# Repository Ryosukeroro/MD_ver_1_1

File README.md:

# MD_ver_1_1
## 偉大なるMD_ver_1_1とは...
モータードライバーを製作して、初めて成功したときのデータです。

# ダウンロード
ダウンロードされる際は、以下のコマンドを実行してください。
```
git clone https://github.com/Ryosukeroro/MD_ver_1_1.git
```

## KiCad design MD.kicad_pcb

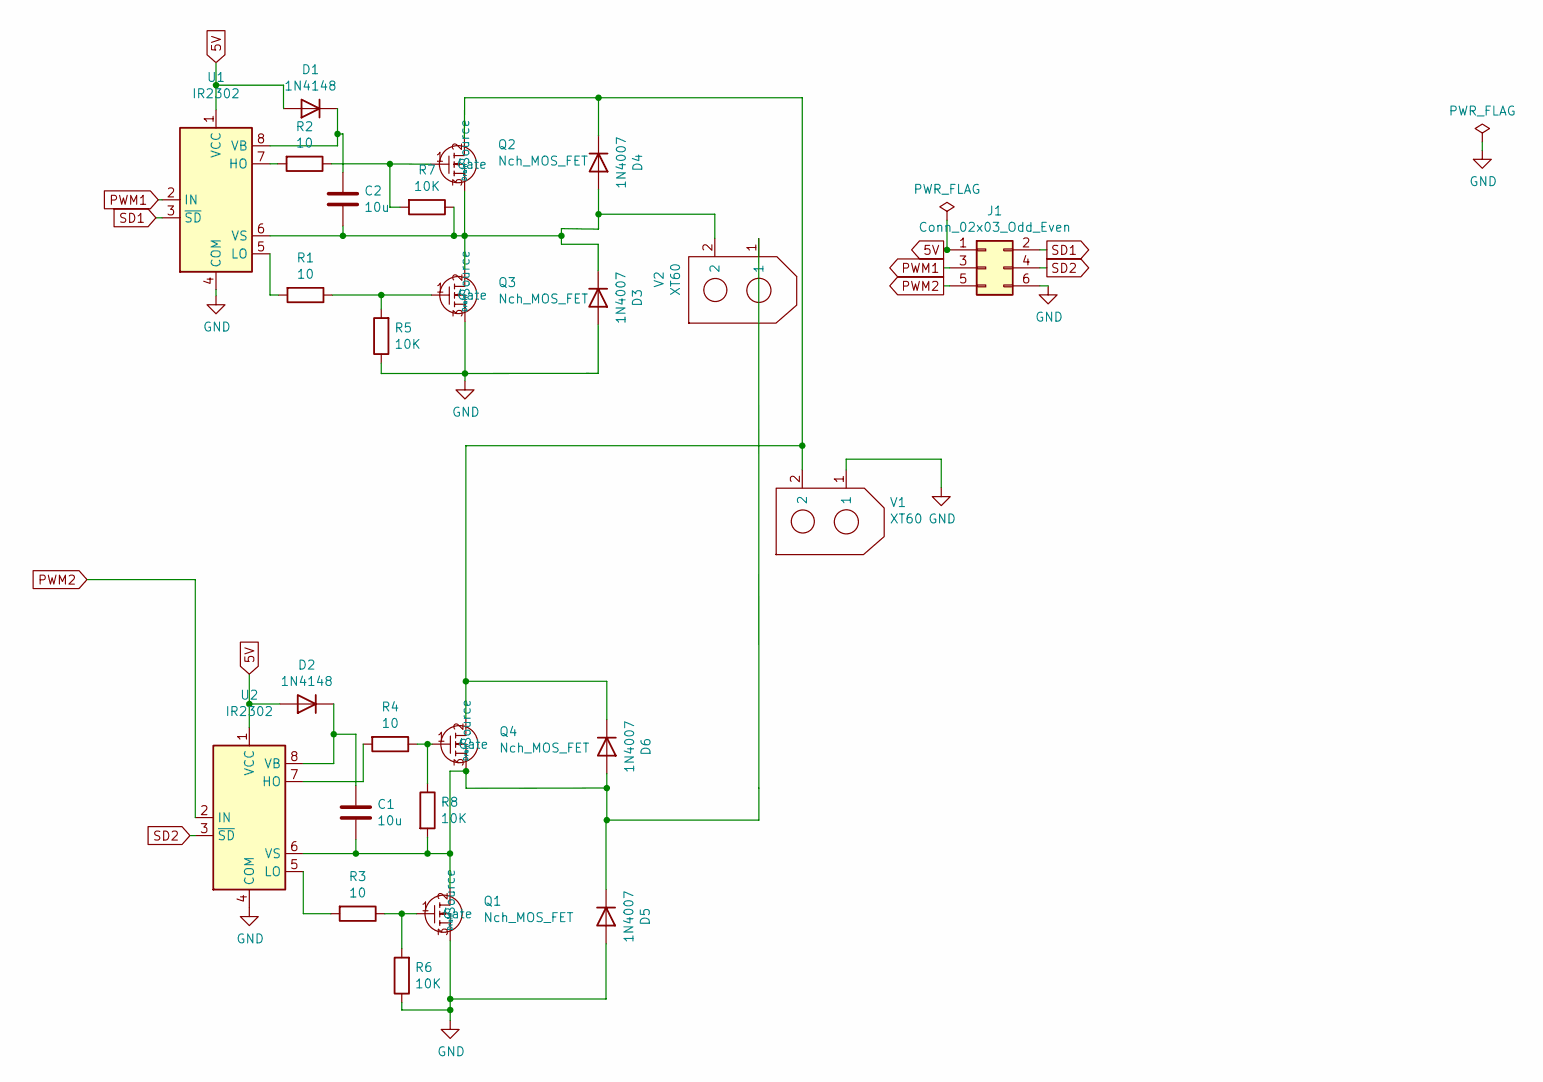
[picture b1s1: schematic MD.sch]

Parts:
C1, C2: 10u; C_Axial_L3.8mm_D2.6mm_P7.50mm_Horizontal
D1, D2: 1N4148; D_DO-35_SOD27_P7.62mm_Horizontal
D3, D4, D5, D6: 1N4007; D_DO-41_SOD81_P10.16mm_Horizontal
J1: Conn_02x03_Odd_Even; PinSocket_2x03_P2.54mm_Vertical
Q1, Q2, Q3, Q4: Nch_MOS_FET; TO-126-3_Vertical
R1, R2, R3, R4: 10; R_2512_6332Metric
R5, R6, R7: 10K; R_0805_2012Metric
R8: 10K; R_Axial_DIN0207_L6.3mm_D2.5mm_P10.16mm_Horizontal
U1, U2: IR2302
V1: XT60; AMASS_XT60-M_1x02_P7.20mm_Vertical
V2: XT60; AMASS_XT60-F_1x02_P7.20mm_Vertical

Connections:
5V: D1.2 (A), D2.2 (A), J1.1, U1.1 (VCC), U2.1 (VCC)
GND: D3.2 (A), D5.2 (A), J1.6, Q1.3 (Source), Q3.3 (Source), R5.1, R6.1, U1.4 (COM), U2.4 (COM), V1.1
unnamed: C1.1, D2.1 (K), U2.8 (VB)
unnamed: C1.2, D5.1 (K), D6.2 (A), Q1.2 (Drain), Q4.3 (Source), R8.2, U2.6 (VS), V2.1
unnamed: C2.1, D1.1 (K), U1.8 (VB)
unnamed: C2.2, D3.1 (K), D4.2 (A), Q2.3 (Source), Q3.2 (Drain), R7.1, U1.6 (VS), V2.2
unnamed: D4.1 (K), D6.1 (K), Q2.2 (Drain), Q4.2 (Drain), V1.2
unnamed: Q1.1 (Gate), R3.1, R6.2
unnamed: Q2.1 (Gate), R2.1, R7.2
unnamed: Q3.1 (Gate), R1.1, R5.2
unnamed: Q4.1 (Gate), R4.1, R8.1
unnamed: R1.2, U1.5 (LO)
unnamed: R2.2, U1.7 (HO)
unnamed: R3.2, U2.5 (LO)
unnamed: R4.2, U2.7 (HO)
PWM1: J1.3, U1.2 (IN)
PWM2: J1.5, U2.2 (IN)
SD1: J1.2, U1.3 (~SD)
SD2: J1.4, U2.3 (~SD)

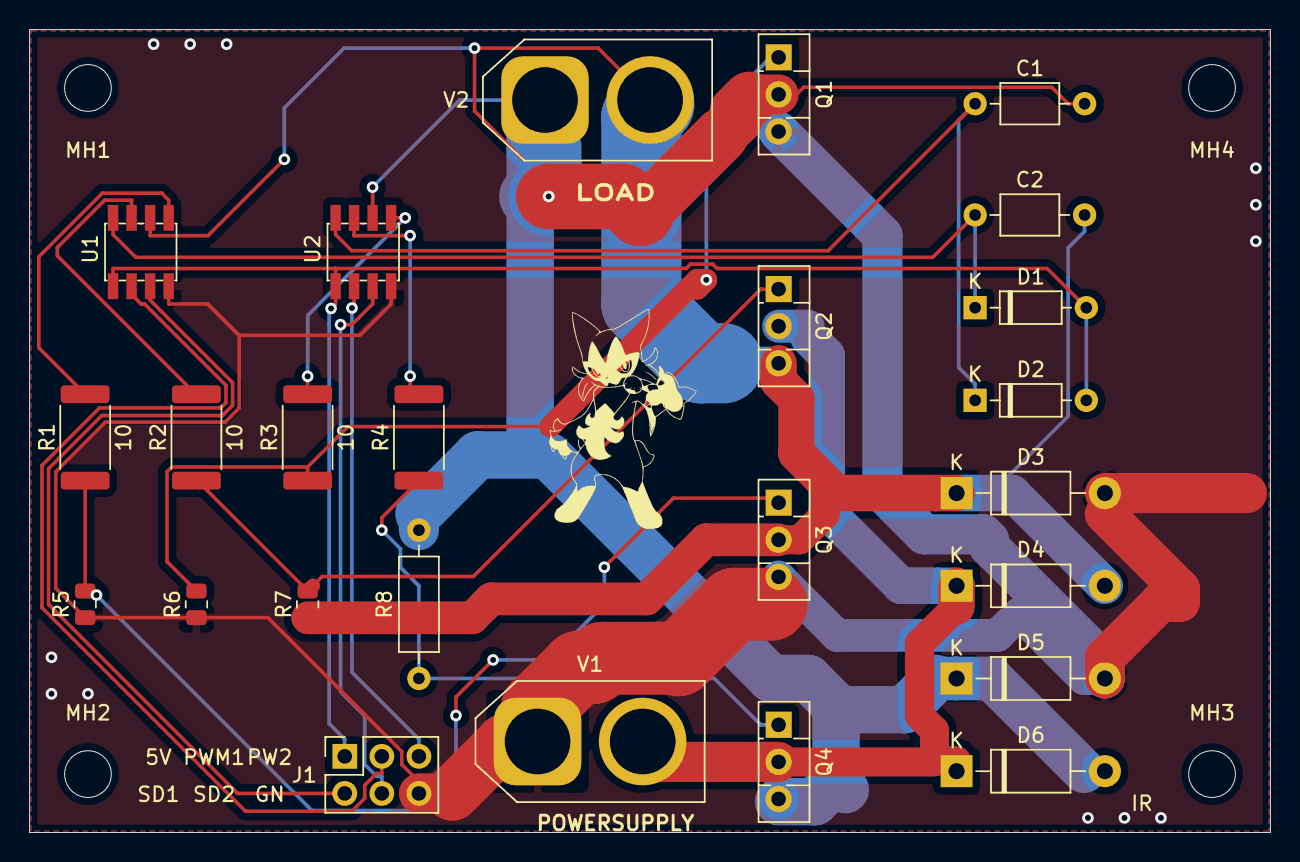
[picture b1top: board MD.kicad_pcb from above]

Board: 2 copper layers, 85.0 x 55.0 mm, 29 parts (0 on the bottom side), 19 nets.

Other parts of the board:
MH1, MH2, MH3, MH4: MountingHole_3.2mm_M3
